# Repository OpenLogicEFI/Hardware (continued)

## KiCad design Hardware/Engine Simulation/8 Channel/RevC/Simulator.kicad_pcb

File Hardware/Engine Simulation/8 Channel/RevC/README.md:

# DetonStim

www.detonationems.com

Engine Simulator for Speeduino fork of Ardustim - https://github.com/speeduino/Ardu-Stim

Fixes:
    Added 5v label to switch selection.
    12v indicator LED routing through D1 as intended.

    Minor layout adjustments.

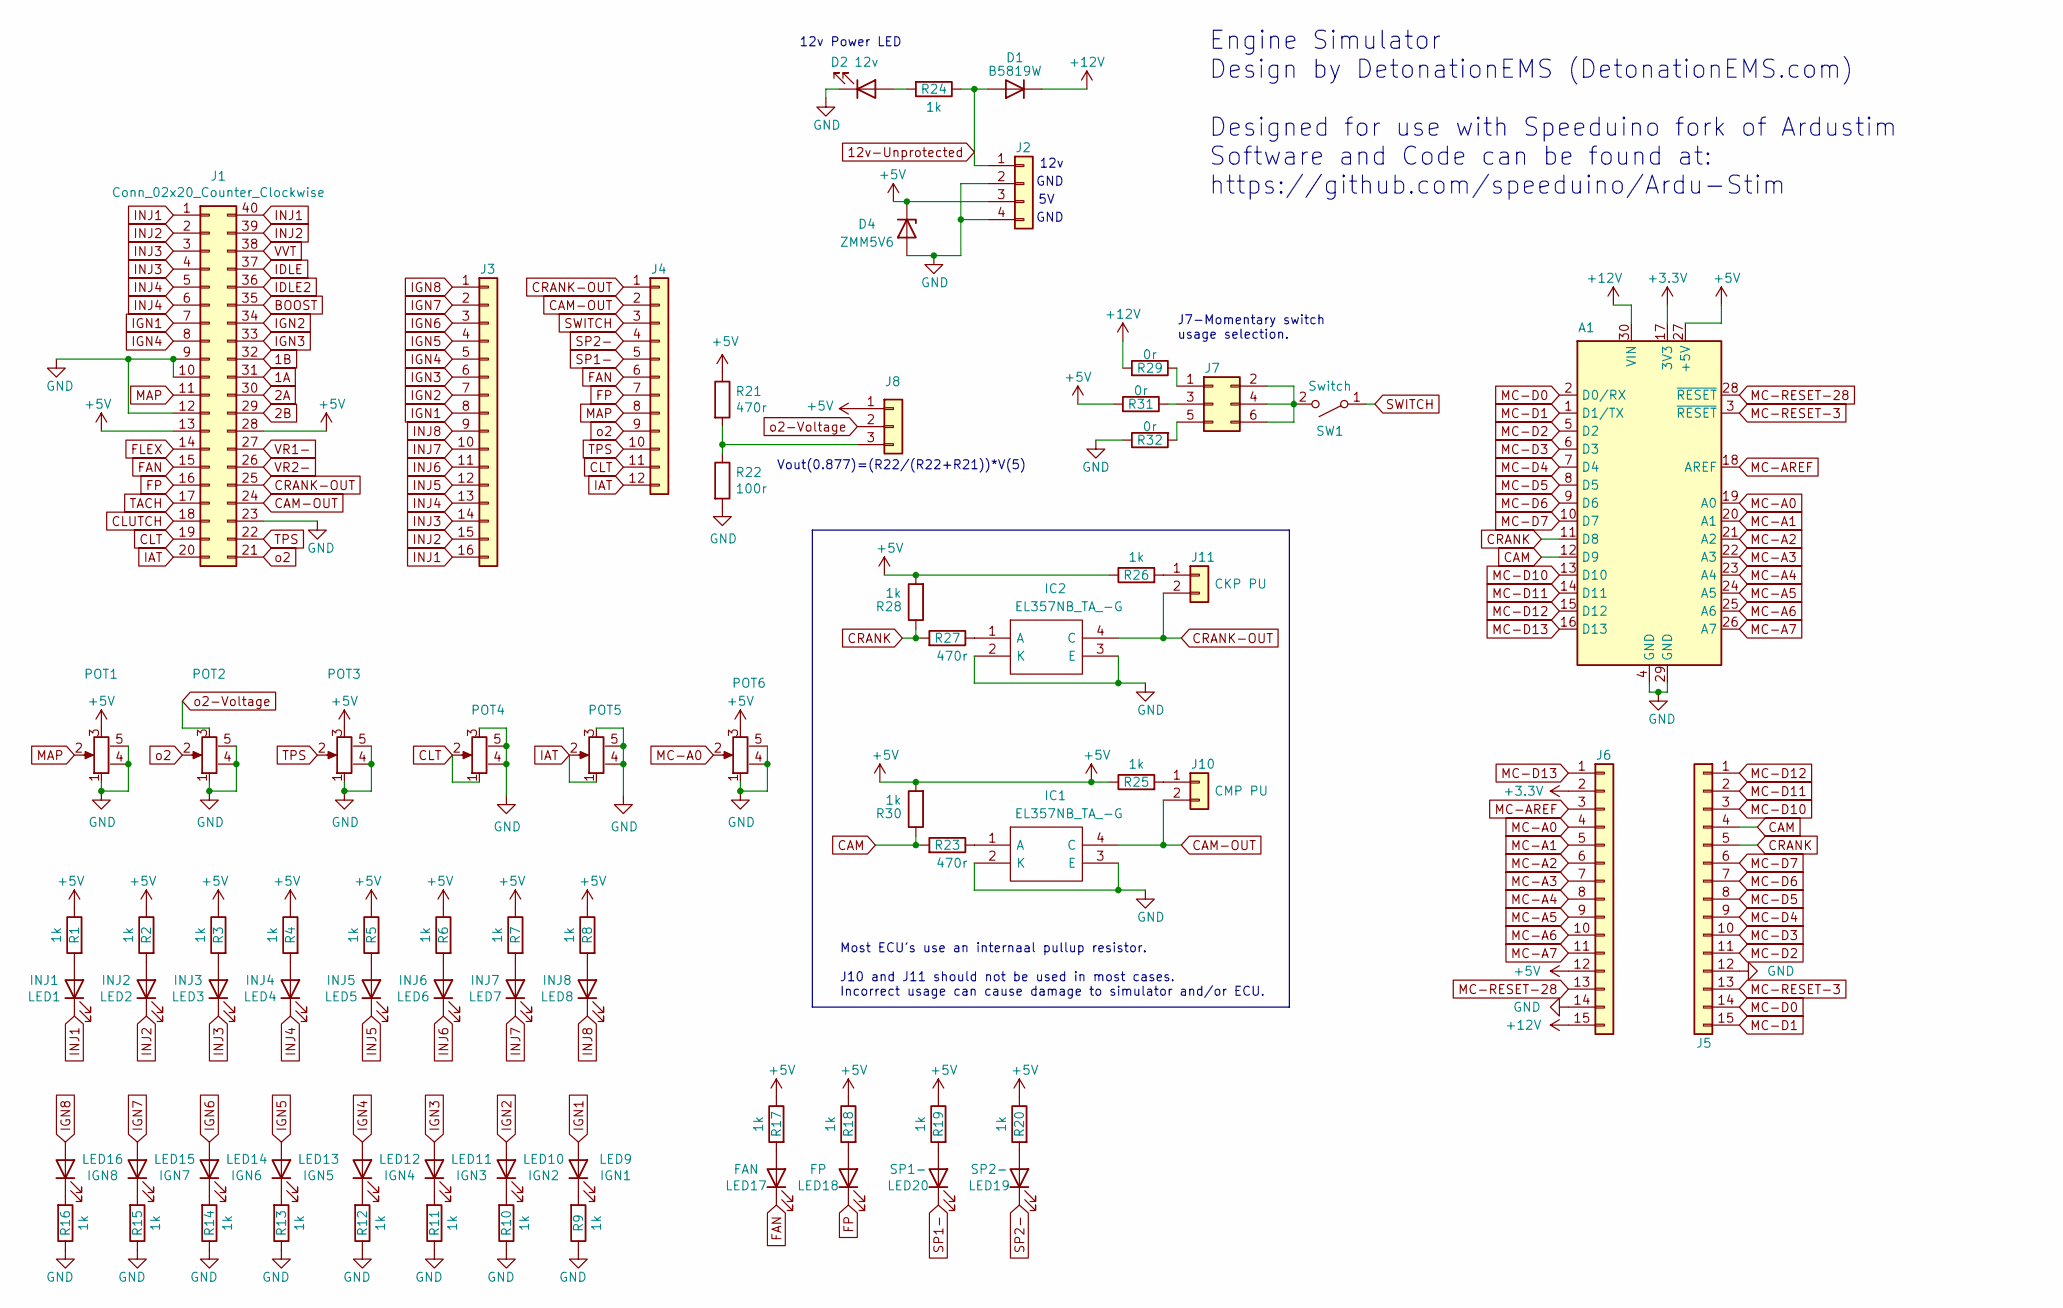
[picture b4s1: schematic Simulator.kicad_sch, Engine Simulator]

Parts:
A1: Arduino_Nano_v3.x; Arduino_Nano
D1: B5819W; D_SOD-123; LCSC C8598
D2: 12v; LED_0603_1608Metric; LCSC C2286
D4: ZMM5V6; D_MiniMELF; LCSC C8062
IC1, IC2: EL357NB_TA_-G; SOP254P700X200-4N; Manufacturer_Part_Number EL357NB(TA)-G; Mouser Part Number 638-EL357NBTAG
J1: Conn_02x20_Counter_Clockwise; IDC-Header_2x20_P2.54mm_Vertical_Speeduino
J2: Conn_01x04; TerminalBlock_Phoenix_PT-1,5-4-3.5-H_1x04_P3.50mm_Horizontal
J3: Conn_01x08; TerminalBlock_Phoenix_PT-1,5-16-3.5-H_1x16_P3.50mm_Horizont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
J4: Conn_01x10; TerminalBlock_Phoenix_PT-1,5-12-3.5-H_1x12_P3.50mm_Horizont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
J5, J6: Conn_01x04; PinSocket_1x15_P2.54mm_Vertical
J7: Conn_01x03; PinSocket 2x03
J8: Conn_01x03; 3-PinSwitch
J10: CMP PU; 1x02-Proto
J11: CKP PU; 1x02-Proto
LED1: INJ1; LED_0603_1608Metric; LCSC C2286
LED2: INJ2; LED_0603_1608Metric; LCSC C2286
LED3: INJ3; LED_0603_1608Metric; LCSC C2286
LED4: INJ4; LED_0603_1608Metric; LCSC C2286
LED5: INJ5; LED_0603_1608Metric; LCSC C2286
LED6: INJ6; LED_0603_1608Metric; LCSC C2286
LED7: INJ7; LED_0603_1608Metric; LCSC C2286
LED8: INJ8; LED_0603_1608Metric; LCSC C2286
LED9: IGN1; LED_0603_1608Metric; LCSC C2286
LED10: IGN2; LED_0603_1608Metric; LCSC C2286
LED11: IGN3; LED_0603_1608Metric; LCSC C2286
LED12: IGN4; LED_0603_1608Metric; LCSC C2286
LED13: IGN5; LED_0603_1608Metric; LCSC C2286
LED14: IGN6; LED_0603_1608Metric; LCSC C2286
LED15: IGN7; LED_0603_1608Metric; LCSC C2286
LED16: IGN8; LED_0603_1608Metric; LCSC C2286
LED17: FAN; LED_0603_1608Metric; LCSC C2286
LED18: FP; LED_0603_1608Metric; LCSC C2286
LED19: SP2-; LED_0603_1608Metric; LCSC C2286
LED20: SP1-; LED_0603_1608Metric; LCSC C2286
POT1: IAT; RV09AF4020KB10K
POT2: CLT; RV09AF4020KB10K
POT3: MAP/SP1; RV09AF4020KB10K
POT4: TPS; RV09AF4020KB10K
POT5: o2; RV09AF4020KB10K
POT6: RPM; RV09AF4020KB10K
R1, R2, R3, R4, R5, R6, R7, R8, R9, R10, R11, R12, R13, R14, R15, R16, R17, R18, R19, R20, R24, R25, R26, R28, R30: 1k; R_0603_1608Metric; LCSC C21190
R21, R23, R27: 470r; R_0603_1608Metric; LCSC C23179
R22: 100r; R_0603_1608Metric; LCSC C22775
R29, R31, R32: 0r; R_0805_2012Metric; Manufacture PN 0805W8F0000T5E; LCSC C17477
SW1: Switch; SW_PUSH_6mm_H9.5mm

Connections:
1A: J1.31
1B: J1.32
2A: J1.30
2B: J1.29
12v-Unprotected: D1.2 (A), J2.1, R24.1
+3.3V: A1.17 (3V3), J6.2
+5V: A1.27 (+5V), D4.1 (K), J1.13, J1.28, J2.3, J6.12, J8.1, POT1.3, POT3.3, POT6.3, R1.1, R2.1, R3.1, R4.1, R5.1, R6.1, R7.1, R8.1, R17.1, R18.1, R19.1, R20.1, R21.1, R25.1, R26.1, R28.2, R30.2, R31.2
+12V: A1.30 (VIN), D1.1 (K), J6.15, R29.2
BOOST: J1.35
CAM: A1.12 (D9), J5.4, R23.2, R30.1
CAM-OUT: IC1.4 (C), J1.24, J4.2, J10.2
CLT: J1.19, J4.11, POT4.1, POT4.2
CLUTCH: J1.18
CRANK: A1.11 (D8), J5.5, R27.2, R28.1
CRANK-OUT: IC2.4 (C), J1.25, J4.1, J11.2
FAN: J1.15, J4.6, LED17.1 (K)
FLEX: J1.14
FP: J1.16, J4.7, LED18.1 (K)
GND: A1.4 (GND), A1.29 (GND), D2.1 (K), D4.2 (A), IC1.2 (K), IC1.3 (E), IC2.2 (K), IC2.3 (E), J1.9, J1.10, J1.12, J1.23, J2.2, J2.4, J5.12, J6.14, POT1.1, POT1.4 (Mounting_Tap), POT1.5 (Mounting_Tap), POT2.1, POT2.4 (Mounting_Tap), POT2.5 (Mounting_Tap), POT3.1, POT3.4 (Mounting_Tap), POT3.5 (Mounting_Tap), POT4.3, POT4.4 (Mounting_Tap), POT4.5 (Mounting_Tap), POT5.3, POT5.4 (Mounting_Tap), POT5.5 (Mounting_Tap), POT6.1, POT6.4 (Mounting_Tap), POT6.5 (Mounting_Tap), R9.1, R10.1, R11.1, R12.1, R13.1, R14.1, R15.1, R16.1, R22.2, R32.1; also elsewhere on the board
IAT: J1.20, J4.12, POT5.1, POT5.2
IDLE: J1.37
IDLE2: J1.36
IGN1: J1.7, J3.8, LED9.2 (A)
IGN2: J1.34, J3.7, LED10.2 (A)
IGN3: J1.33, J3.6, LED11.2 (A)
IGN4: J1.8, J3.5, LED12.2 (A)
IGN5: J3.4, LED13.2 (A)
IGN6: J3.3, LED14.2 (A)
IGN7: J3.2, LED15.2 (A)
IGN8: J3.1, LED16.2 (A)
INJ1: J1.1, J1.40, J3.16, LED1.1 (K)
INJ2: J1.2, J1.39, J3.15, LED2.1 (K)
INJ3: J1.3, J1.4, J3.14, LED3.1 (K)
INJ4: J1.5, J1.6, J3.13, LED4.1 (K)
INJ5: J3.12, LED5.1 (K)
INJ6: J3.11, LED6.1 (K)
INJ7: J3.10, LED7.1 (K)
INJ8: J3.9, LED8.1 (K)
MAP: J1.11, J4.8, POT1.2
MC-A0: A1.19 (A0), J6.4, POT6.2
MC-A1: A1.20 (A1), J6.5
MC-A2: A1.21 (A2), J6.6
MC-A3: A1.22 (A3), J6.7
MC-A4: A1.23 (A4), J6.8
MC-A5: A1.24 (A5), J6.9
MC-A6: A1.25 (A6), J6.10
MC-A7: A1.26 (A7), J6.11
MC-AREF: A1.18 (AREF), J6.3
MC-D0: A1.2 (D0/RX), J5.14
MC-D1: A1.1 (D1/TX), J5.15
MC-D2: A1.5 (D2), J5.11
MC-D3: A1.6 (D3), J5.10
MC-D4: A1.7 (D4), J5.9
MC-D5: A1.8 (D5), J5.8
MC-D6: A1.9 (D6), J5.7
MC-D7: A1.10 (D7), J5.6
MC-D10: A1.13 (D10), J5.3
MC-D11: A1.14 (D11), J5.2
MC-D12: A1.15 (D12), J5.1
MC-D13: A1.16 (D13), J6.1
MC-RESET-3: A1.3 (~RESET), J5.13
MC-RESET-28: A1.28 (~RESET), J6.13
unnamed: D2.2 (A), R24.2
unnamed: IC1.1 (A), R23.1
unnamed: IC2.1 (A), R27.1
unnamed: J7.1, R29.1
unnamed: J7.2, J7.4, J7.6, SW1.2 (B)
unnamed: J7.3, R31.1
unnamed: J7.5, R32.2
unnamed: J8.3, R21.2, R22.1
unnamed: J10.1, R25.2
unnamed: J11.1, R26.2
unnamed: LED1.2 (A), R1.2
unnamed: LED2.2 (A), R2.2
unnamed: LED3.2 (A), R3.2
unnamed: LED4.2 (A), R4.2
unnamed: LED5.2 (A), R5.2
unnamed: LED6.2 (A), R6.2
unnamed: LED7.2 (A), R7.2
unnamed: LED8.2 (A), R8.2
unnamed: LED9.1 (K), R9.2
unnamed: LED10.1 (K), R10.2
unnamed: LED11.1 (K), R11.2
unnamed: LED12.1 (K), R12.2
unnamed: LED13.1 (K), R13.2
unnamed: LED14.1 (K), R14.2
unnamed: LED15.1 (K), R15.2
unnamed 87: LED16.1 (K), R16.2; also elsewhere on the board
unnamed: LED17.2 (A), R17.2
unnamed: LED18.2 (A), R18.2
unnamed: LED19.2 (A), R20.2
unnamed: LED20.2 (A), R19.2
SP1-: J4.5, LED20.1 (K)
SP2-: J4.4, LED19.1 (K)
SWITCH: J4.3, SW1.1 (A)
TACH: J1.17
TPS: J1.22, J4.10, POT3.2
VR1-: J1.27
VR2-: J1.26
VVT: J1.38
o2: J1.21, J4.9, POT2.2
o2-Voltage: J8.2, POT2.3

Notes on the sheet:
Most ECU's use an internaal pullup resistor. J10 and J11 should not be used in most cases. Incorrect usage can cause damage to simulator and/or ECU.
12v
Engine Simulator Design by DetonationEMS (DetonationEMS.com) Designed for use with Speeduino fork of Ardustim Software and Code can be found at: https://github.com/speeduino/Ardu-Stim
GND
12v Power LED
J7-Momentary switch usage selection.
Vout(0.877)=(R22/(R22+R21))*V(5)

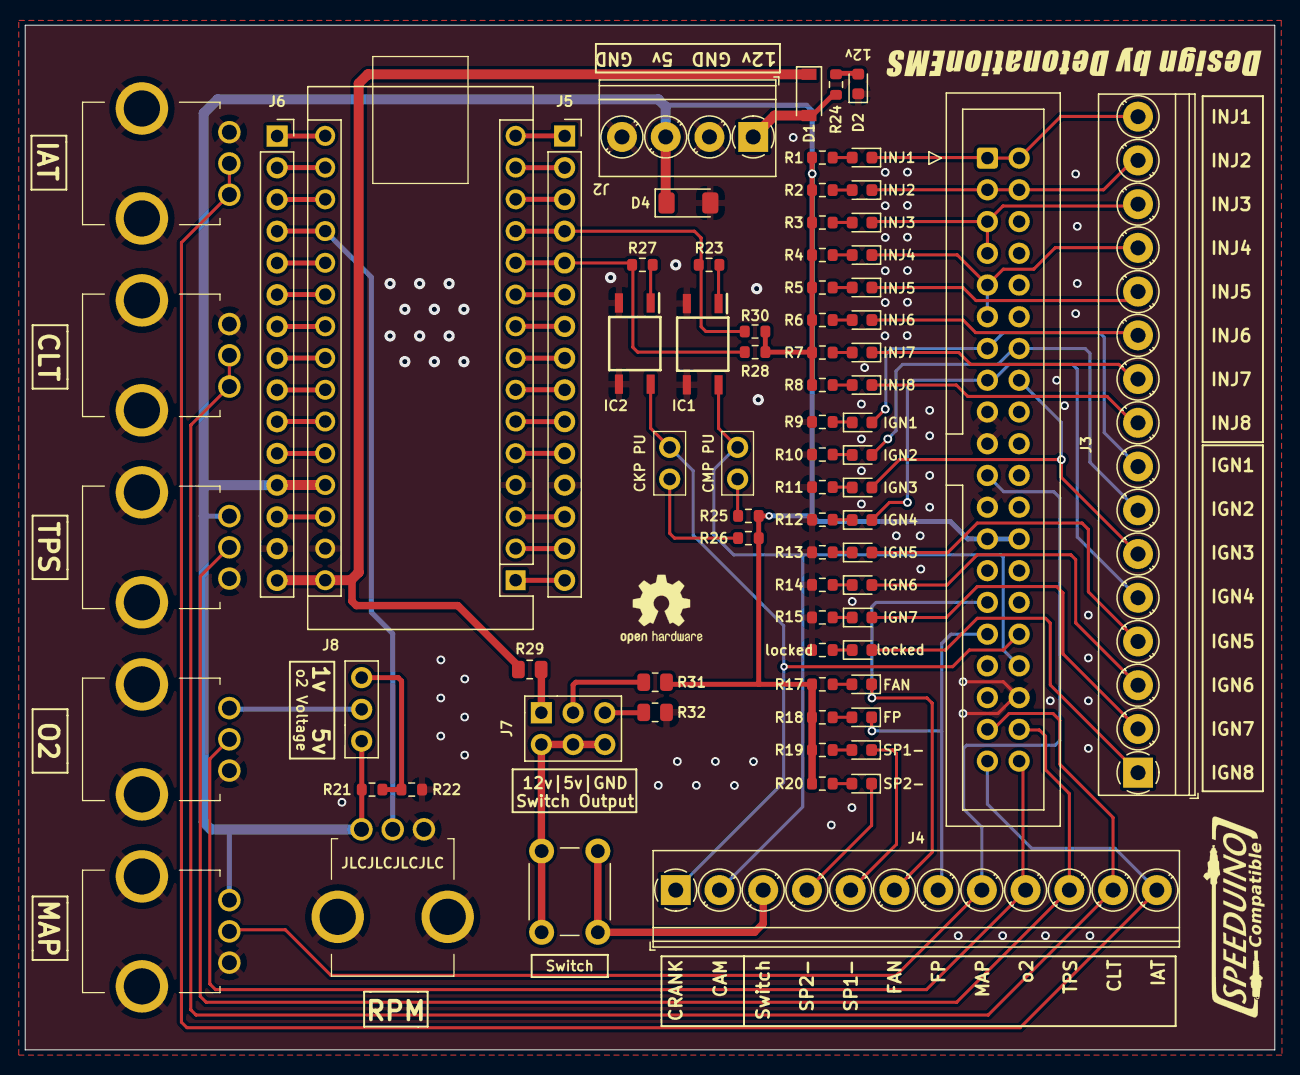
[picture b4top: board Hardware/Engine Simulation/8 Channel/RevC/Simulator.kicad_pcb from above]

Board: 2 copper layers, 100.0 x 82.0 mm, 78 parts (0 on the bottom side), 89 nets.

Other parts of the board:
G1: Logo_Open_Hardware_Small; Design by 30mm
G2: Logo_Open_Hardware_Small; SpeeduinoCompatible-17mm
G3: Logo_Open_Hardware_Small; OSHW-Logo2_7.3x6mm_SilkScreen
locked: 1k; R_0603_1608Metric

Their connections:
GND: locked.1; also elsewhere on the board
unnamed 87: locked.2; also elsewhere on the board

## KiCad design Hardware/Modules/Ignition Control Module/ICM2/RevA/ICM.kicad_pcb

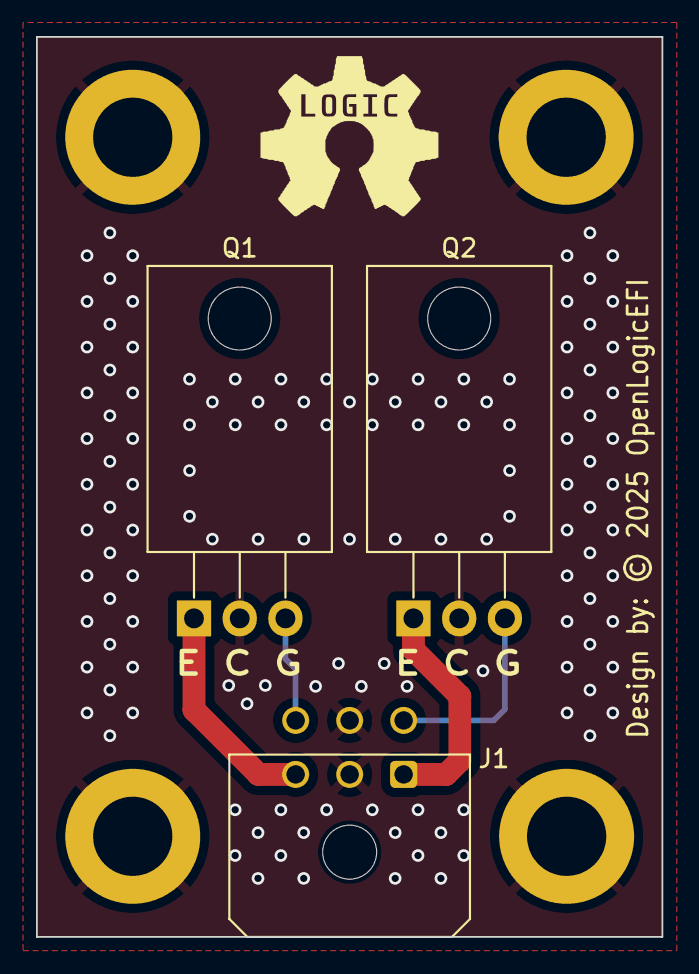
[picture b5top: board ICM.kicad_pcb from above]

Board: 2 copper layers, 34.8 x 50.0 mm, 9 parts (1 on the bottom side), 5 nets.

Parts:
G01: LOGO; open-logic-10
G2: LOGO; SpeeduinoCompatible-17mm
H1, H2, H3, H4: MountingHole_Pad; MountingHole_4.3mm_M4_DIN965_Pad
J1: Conn_01x06; Molex_Micro-Fit_3.0_43045-0600_2x03_P3.00mm_Horizontal
Q1, Q2: ISL9V3040P3; TO-220-3_Horizontal_TabDown

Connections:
GND: H1.1, H2.1, H3.1, H4.1, J1.2, J1.5, Q1.2 (COLLECTOR), Q2.2 (COLLECTOR)
InputA: J1.6, Q1.3 (GATE)
InputB: J1.4, Q2.3 (GATE)
OutputA: J1.3, Q1.1 (EMITTER)
OutputB: J1.1, Q2.1 (EMITTER)

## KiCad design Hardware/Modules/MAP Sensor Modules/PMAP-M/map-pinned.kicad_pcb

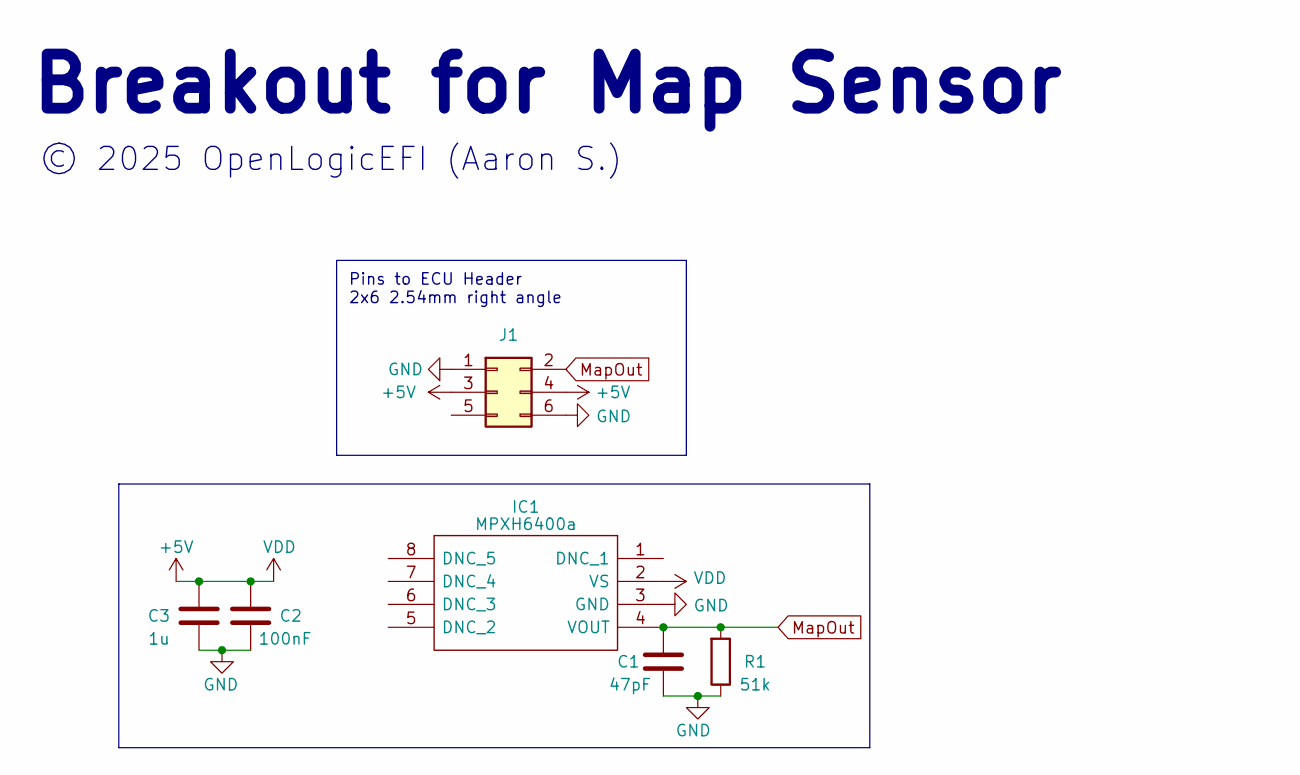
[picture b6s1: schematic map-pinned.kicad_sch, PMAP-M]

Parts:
C1: 47pF; C_0402_1005Metric; Manufacture Part Number 0402CG470J500NT; LCSC C1567
C2: 100nF; C_0402_1005Metric; Manufacture Part Number CL05B104KO5NNNC; LCSC C1525
C3: 1u; C_0805_2012Metric; Manufacture Part Number CL21B105KBFNNNE; LCSC C28323
IC1: MPXH6400a; MPXHxxx_Handsoldering
J1: Conn_02x03_Odd_Even; PinHeader_2x03_P2.54mm_Horizontal
R1: 51k; R_0402_1005Metric; Manufacture Part Number 0402WGF5102TCE; LCSC C25794

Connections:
+5V: C2.1, C3.1, IC1.2 (VS), J1.3, J1.4
GND: C1.2, C2.2, C3.2, IC1.3 (GND), J1.1, J1.6, R1.1
MapOut: C1.1, IC1.4 (VOUT), J1.2, R1.2

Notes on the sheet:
Pins to ECU Header 2x6 2.54mm right angle
© 2025 OpenLogicEFI (Aaron S.)
Breakout for Map Sensor

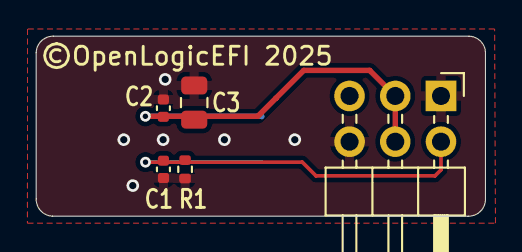
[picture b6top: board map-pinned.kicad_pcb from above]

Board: 2 copper layers, 25.0 x 10.0 mm, 6 parts (1 on the bottom side), 3 nets.

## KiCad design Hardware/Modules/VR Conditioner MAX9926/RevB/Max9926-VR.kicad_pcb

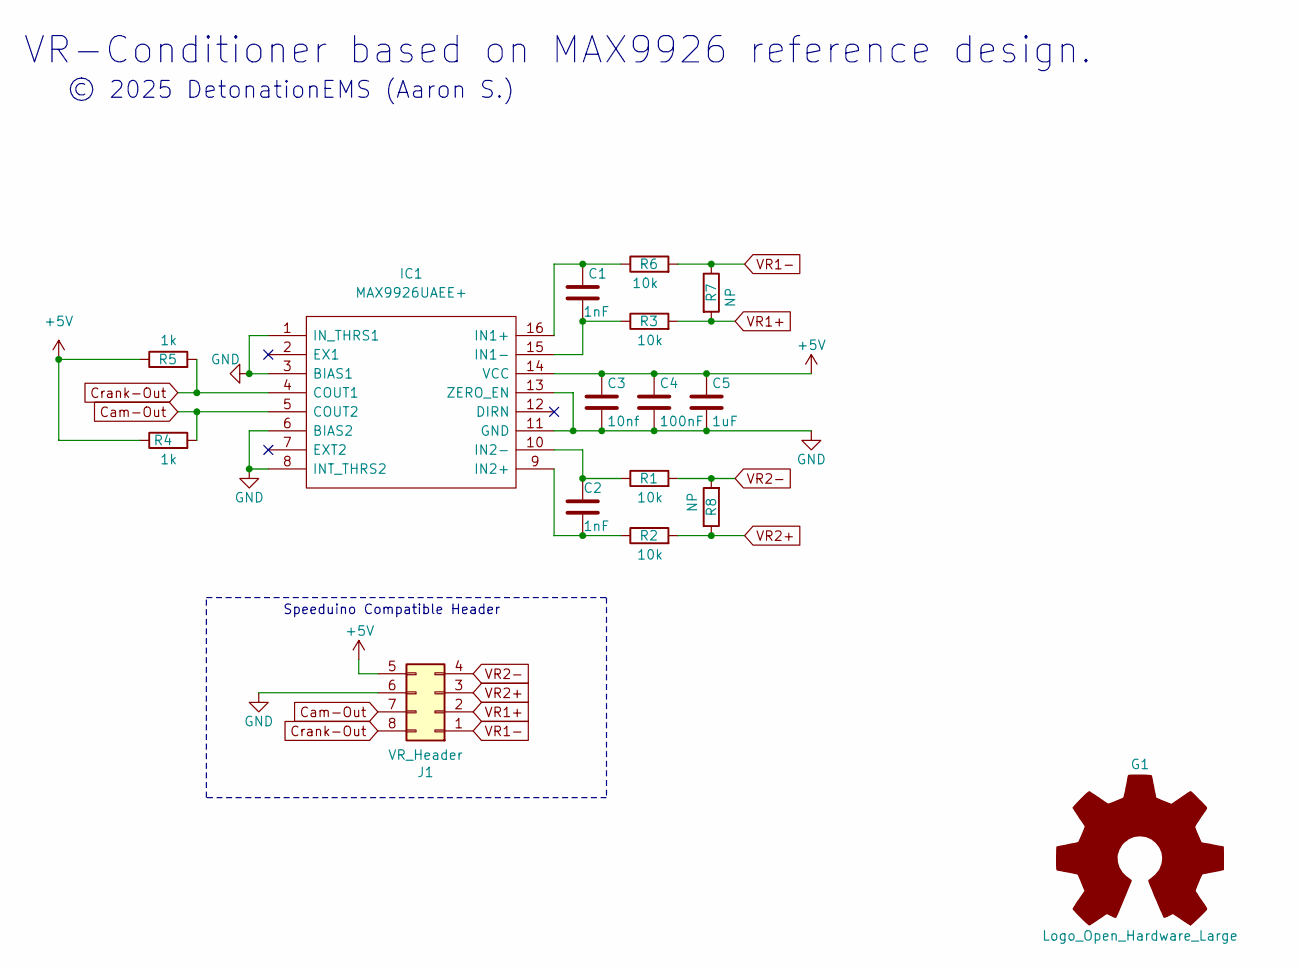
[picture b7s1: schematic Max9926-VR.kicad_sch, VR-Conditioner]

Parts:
C1, C2: 1nF; C_0603_1608Metric; LCSC C1588
C3: 10nf; C_0603_1608Metric; LCSC C57112
C4: 100nF; C_0603_1608Metric; LCSC C14663
C5: 1uF; C_0603_1608Metric; LCSC C15849
G1: Logo_Open_Hardware_Large; SpeeduinoCompatible-17mm
IC1: MAX9926UAEE+; MAX9926-HandSoldering; MFG Part Num MAX9926UAEE+
J1: VR_Header; Socket_VRConditioner
R1, R2, R3, R6: 10k; R_1206_3216Metric; LCSC C17902
R4, R5: 1k; R_0402_1005Metric; LCSC C11702
R7, R8: NP; R_Axial_DIN0207_L6.3mm_D2.5mm_P7.62mm_Horizontal

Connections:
+5V: C3.1, C4.1, C5.1, IC1.14 (VCC), J1.5, R4.1, R5.1
Cam-Out: IC1.5 (COUT2), J1.7, R4.2
Crank-Out: IC1.4 (COUT1), J1.8, R5.2
GND: C3.2, C4.2, C5.2, IC1.1 (IN_THRS1), IC1.3 (BIAS1), IC1.6 (BIAS2), IC1.8 (INT_THRS2), IC1.11 (GND), IC1.13 (ZERO_EN), J1.6
unnamed: C1.1, IC1.16 (IN1+), R6.1
unnamed: C1.2, IC1.15 (IN1-), R3.1
unnamed: C2.2, IC1.9 (IN2+), R2.1
unnamed: C2.1, IC1.10 (IN2-), R1.1
VR1+: J1.2, R3.2, R7.2
VR1-: J1.1, R6.2, R7.1
VR2+: J1.3, R2.2, R8.1
VR2-: J1.4, R1.2, R8.2

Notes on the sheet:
© 2025 DetonationEMS (Aaron S.)
Speeduino Compatible Header
VR-Conditioner based on MAX9926 reference design.

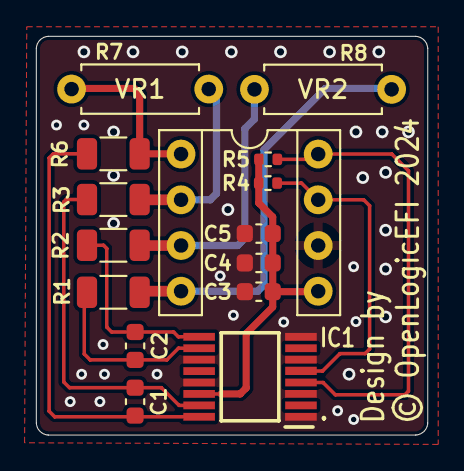
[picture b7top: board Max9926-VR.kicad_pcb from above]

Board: 2 copper layers, 21.7 x 22.1 mm, 16 parts (1 on the bottom side), 12 nets.
